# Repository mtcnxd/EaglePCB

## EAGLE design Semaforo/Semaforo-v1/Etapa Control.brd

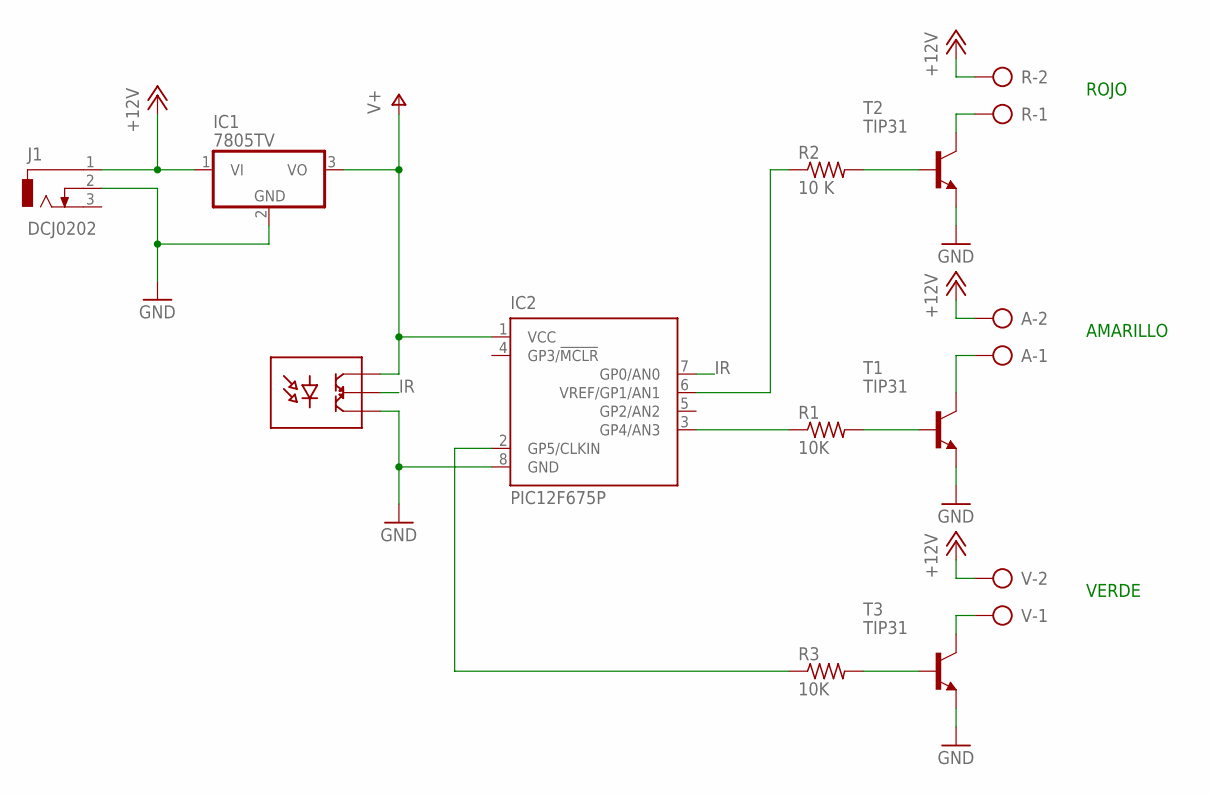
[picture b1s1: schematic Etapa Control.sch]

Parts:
A: AK300/2
IC1: 7805TV; TO220V
IC2: PIC12F675P; DIL8
J1: DCJ0202
LF1838: LF1838
R: AK300/2
R1, R3: 10K; 0204/7
R2: 10 K; 0204/7
T1, T2, T3: TIP31; TO220
V: AK300/2

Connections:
+12V: A.2, IC1.1 (VI), J1.1, R.2, V.2
GND: IC1.2 (GND), IC2.8 (GND), J1.2, LF1838.GND, T1.3 (E), T2.3 (E), T3.3 (E)
IR: IC2.7 (GP0/AN0), LF1838.VOUT
unnamed: R1.2, T1.1 (B)
unnamed: R2.2, T2.1 (B)
unnamed: R3.2, T3.1 (B)
unnamed: T3.2 (C), V.1
unnamed: R.1, T2.2 (C)
unnamed: A.1, T1.2 (C)
unnamed: IC2.6 (VREF/GP1/AN1), R2.1
unnamed: IC2.3 (GP4/AN3), R1.1
unnamed: IC2.2 (GP5/CLKIN), R3.1
V+: IC1.3 (VO), IC2.1 (VCC), LF1838.VCC

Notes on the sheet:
ROJO
AMARILLO
VERDE

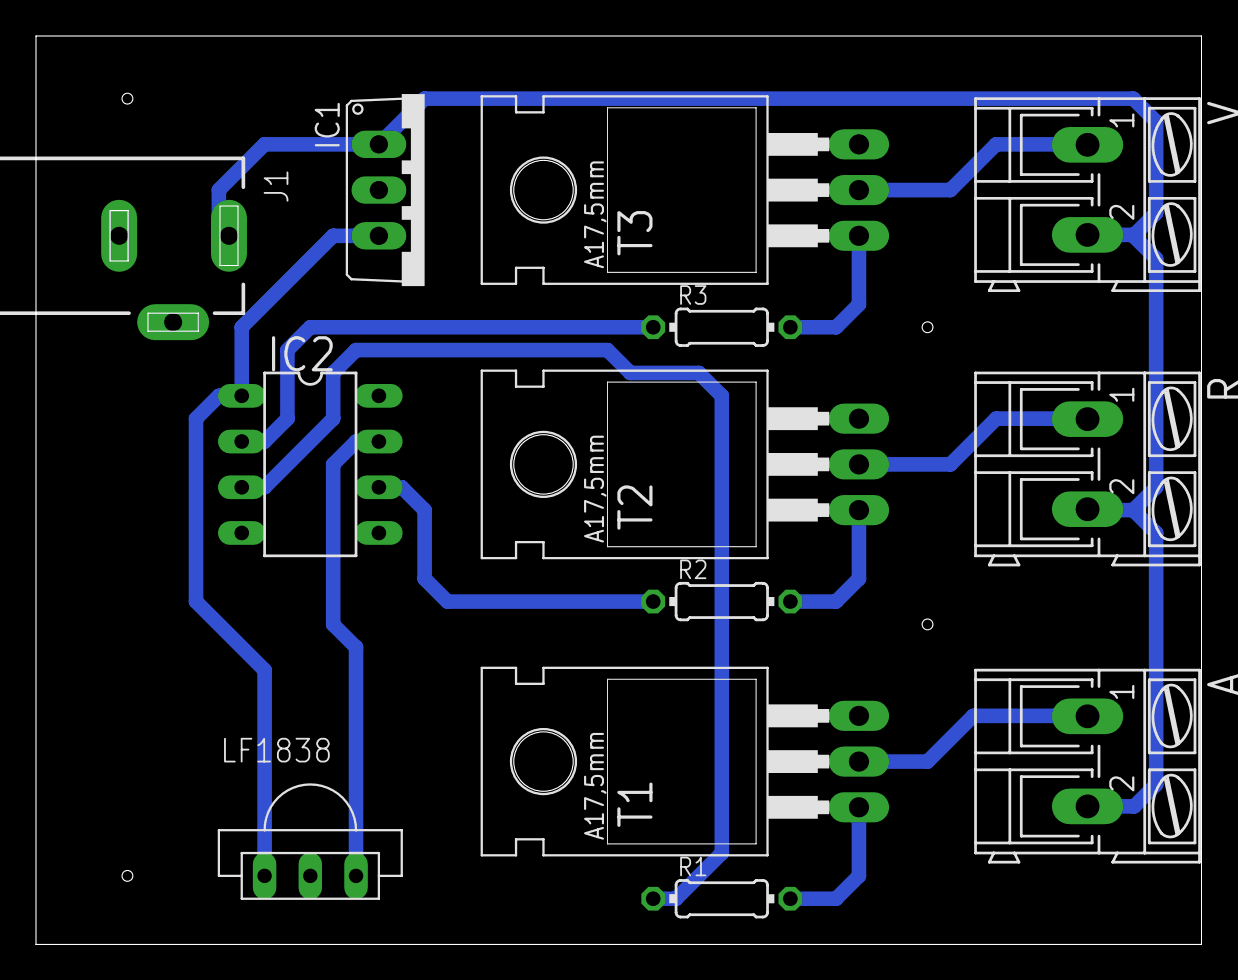
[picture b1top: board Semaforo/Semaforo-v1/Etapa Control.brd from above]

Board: 2 copper layers, 64.8 x 50.5 mm, 13 parts (0 on the bottom side), 13 nets.

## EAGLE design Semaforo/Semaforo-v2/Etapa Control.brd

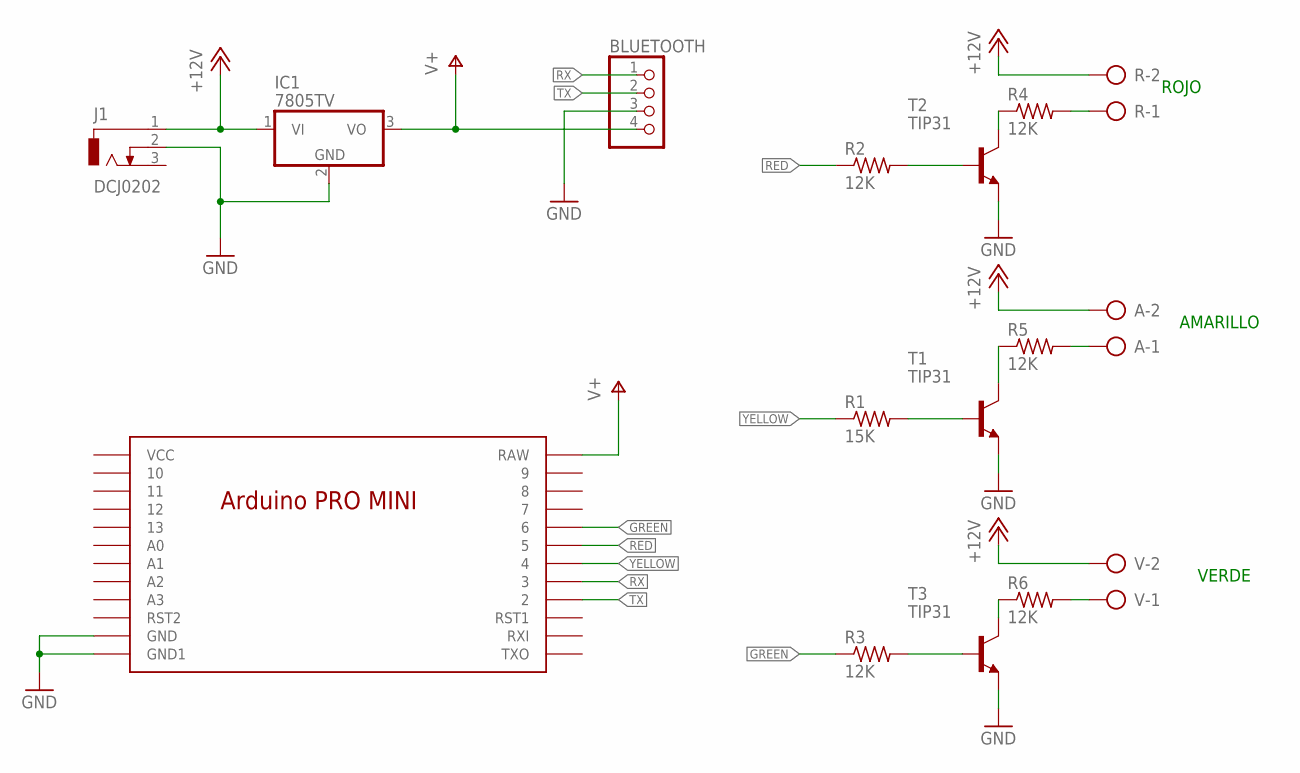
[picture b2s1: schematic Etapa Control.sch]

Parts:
A: AK300/2
BLUETOOTH: PINHD-1X4; 1X04
IC1: 7805TV; TO220V
J1: DCJ0202
R: AK300/2
R1: 15K; 0204/7
R2, R3, R4, R5, R6: 12K; 0204/7
T1, T2, T3: TIP31; TO220
U$1: NANO
V: AK300/2

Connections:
+12V: A.2, IC1.1 (VI), J1.1, R.2, V.2
GND: BLUETOOTH.3, IC1.2 (GND), J1.2, T1.3 (E), T2.3 (E), T3.3 (E), U$1.GND1 (GND), U$1.GND2 (GND1)
GREEN: R3.1, U$1.6
unnamed: R1.2, T1.1 (B)
unnamed: R2.2, T2.1 (B)
unnamed: R3.2, T3.1 (B)
unnamed: R6.1, T3.2 (C)
unnamed: R4.1, T2.2 (C)
unnamed: R5.1, T1.2 (C)
unnamed: R.1, R4.2
unnamed: A.1, R5.2
unnamed: R6.2, V.1
RED: R2.1, U$1.5
RX: BLUETOOTH.1, U$1.3
TX: BLUETOOTH.2, U$1.2
V+: BLUETOOTH.4, IC1.3 (VO), U$1.RAW
YELLOW: R1.1, U$1.4

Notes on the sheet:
ROJO
AMARILLO
VERDE

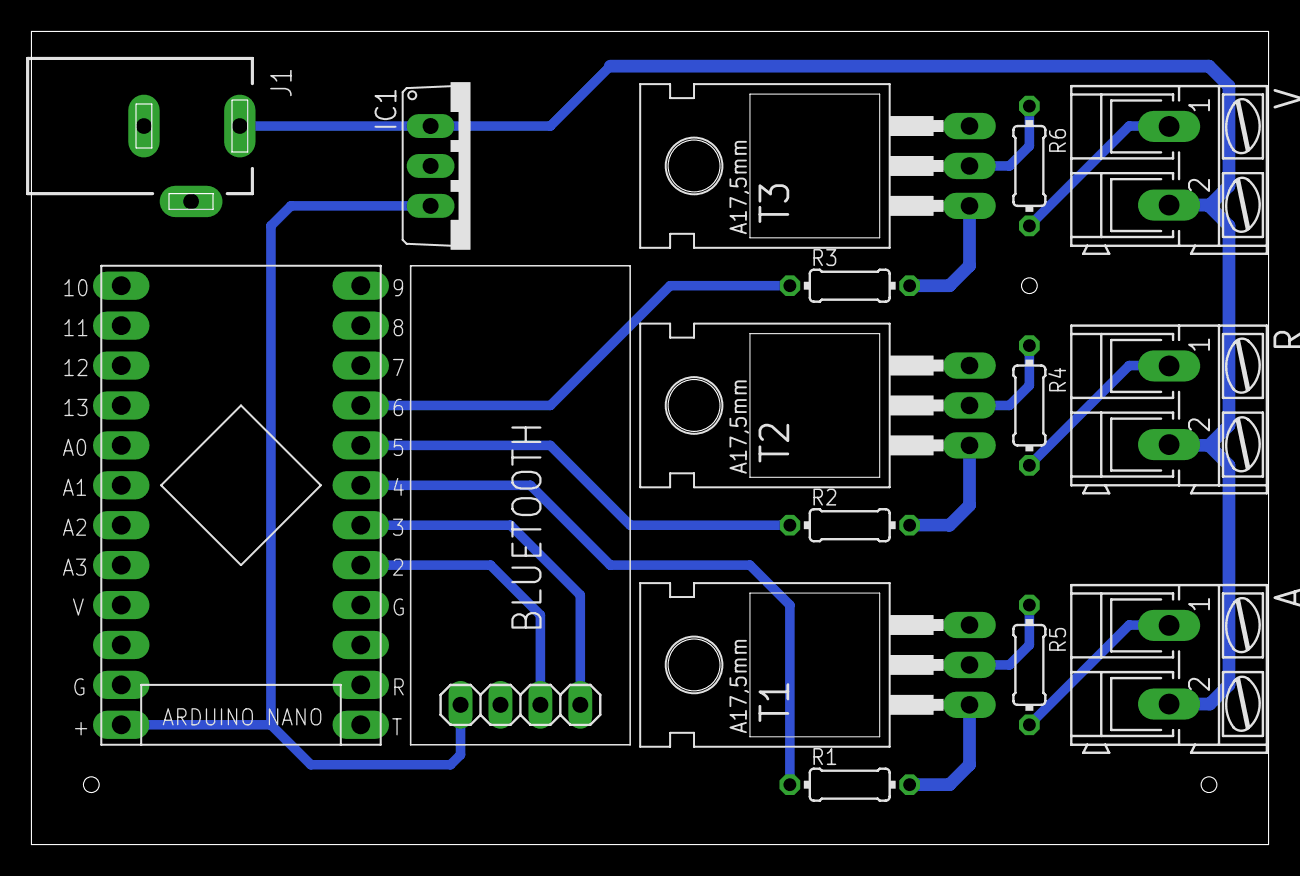
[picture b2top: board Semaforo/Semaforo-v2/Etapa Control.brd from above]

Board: 2 copper layers, 78.7 x 51.7 mm, 16 parts (0 on the bottom side), 17 nets.

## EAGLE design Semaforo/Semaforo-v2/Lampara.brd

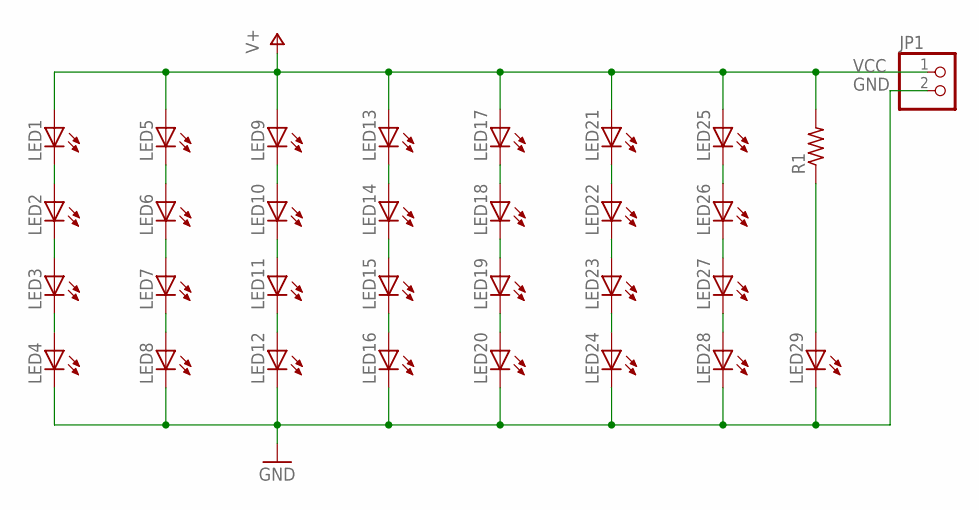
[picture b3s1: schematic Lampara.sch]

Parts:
JP1: PINHD-1X2/90; 1X02/90
LED1, LED2, LED3, LED4, LED5, LED6, LED7, LED8, LED9, LED10, LED11, LED12, LED13, LED14, LED15, LED16, LED17, LED18, LED19, LED20, LED21, LED22, LED23, LED24, LED25, LED26, LED27, LED28, LED29: LED5MM
R1: R-US_0204/7; 0204/7

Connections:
GND: JP1.2, LED4.K (C), LED8.K (C), LED12.K (C), LED16.K (C), LED20.K (C), LED24.K (C), LED28.K (C), LED29.K (C)
unnamed: LED15.K (C), LED16.A
unnamed: LED1.K (C), LED2.A
unnamed: LED2.K (C), LED3.A
unnamed: LED3.K (C), LED4.A
unnamed: LED5.K (C), LED6.A
unnamed: LED6.K (C), LED7.A
unnamed: LED7.K (C), LED8.A
unnamed: LED10.K (C), LED11.A
unnamed: LED9.K (C), LED10.A
unnamed: LED11.K (C), LED12.A
unnamed: LED14.K (C), LED15.A
unnamed: LED13.K (C), LED14.A
unnamed: LED25.K (C), LED26.A
unnamed: LED17.K (C), LED18.A
unnamed: LED18.K (C), LED19.A
unnamed: LED29.A, R1.1
unnamed: LED19.K (C), LED20.A
unnamed: LED22.K (C), LED23.A
unnamed: LED23.K (C), LED24.A
unnamed: LED27.K (C), LED28.A
unnamed: LED26.K (C), LED27.A
unnamed: LED21.K (C), LED22.A
VCC: JP1.1, LED1.A, LED5.A, LED9.A, LED13.A, LED17.A, LED21.A, LED25.A, R1.2

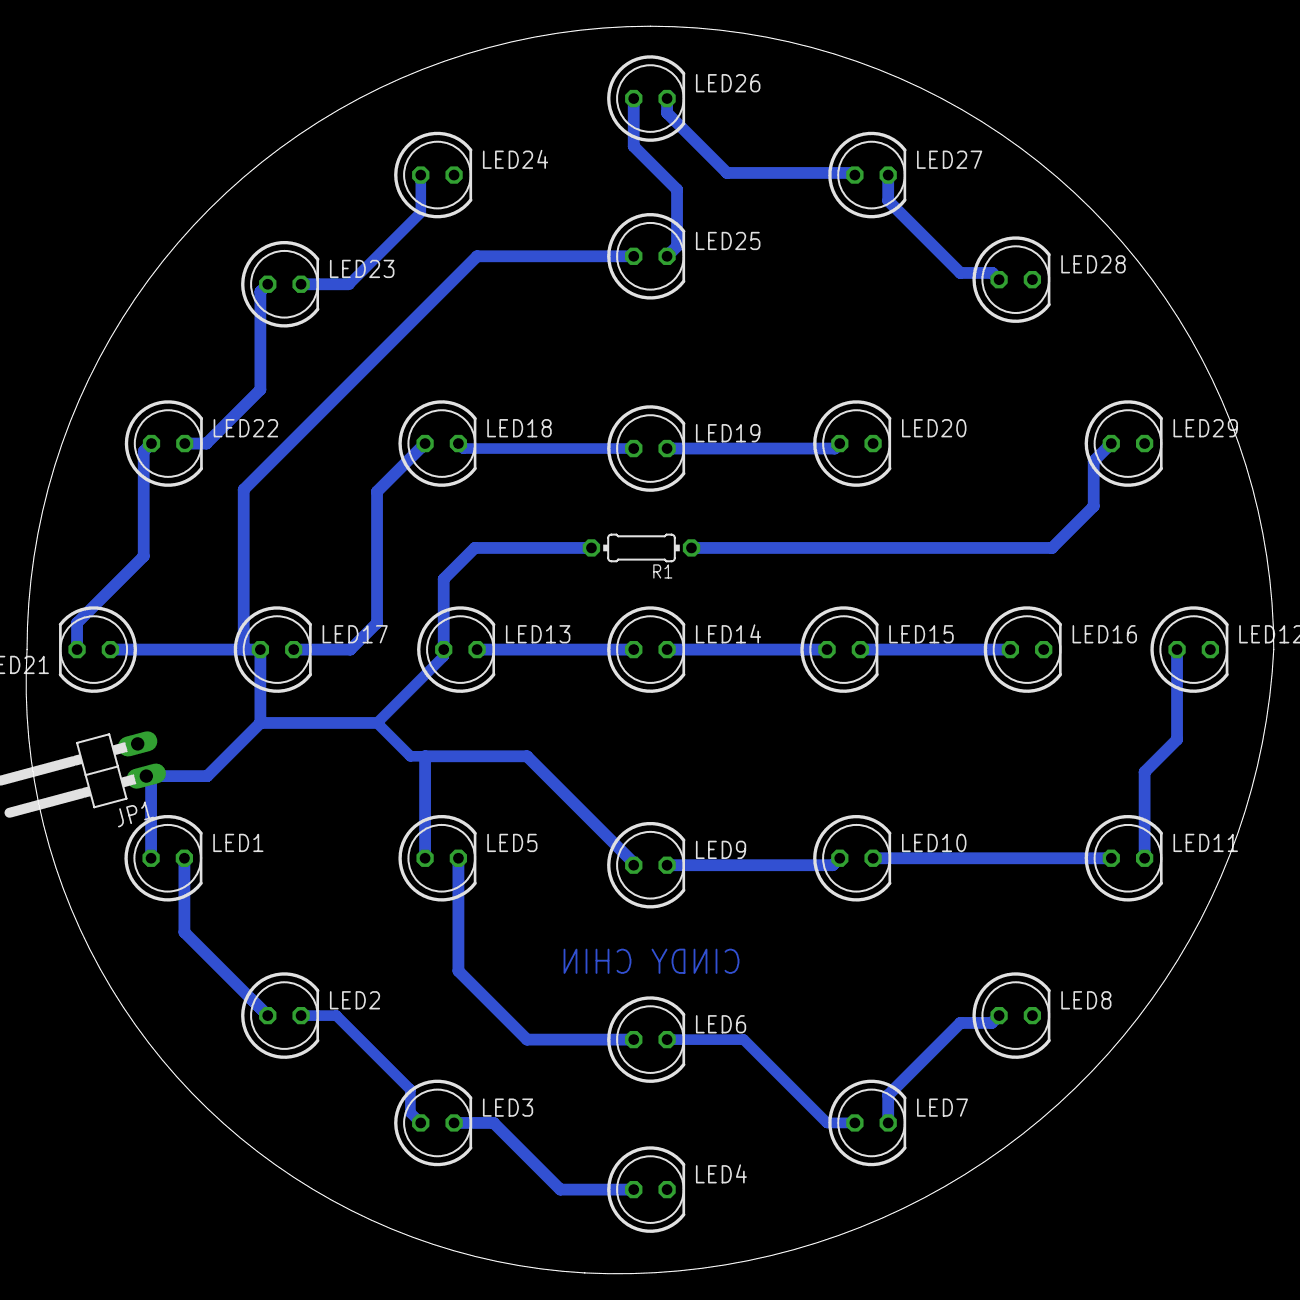
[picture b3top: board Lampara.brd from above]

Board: 2 copper layers, 95.1 x 95.1 mm, 31 parts (0 on the bottom side), 24 nets.

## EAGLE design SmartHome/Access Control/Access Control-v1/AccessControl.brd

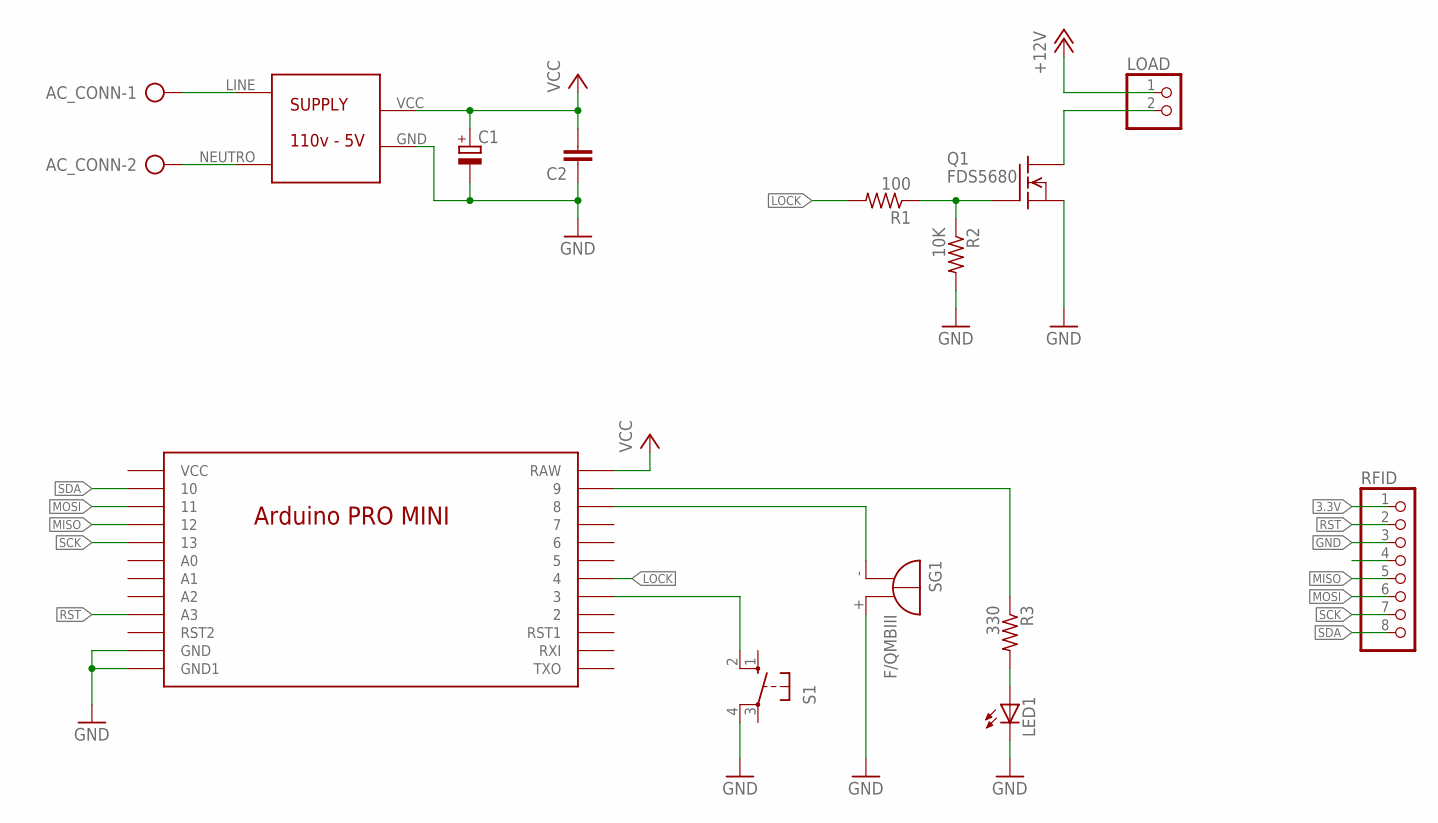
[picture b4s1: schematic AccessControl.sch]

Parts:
AC_CONN: AK300/2
C1: CPOL-EUE2.5-6; E2,5-6
C2: C2.5/2; C2.5-2
LED1: LED3MM
LOAD: PINHD-1X2; 1X02
Q1: FDS5680; SO-8
R1: 100; 0204/7
R2: 10K; 0204/7
R3: 330; 0204/7
RFID: PINHD-1X8; 1X08
S1: 10-XX; B3F-10XX
SG1: F/QMBIII
U$1: NANO
U$2: SUPPLY5V

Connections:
3.3V: RFID.1
+12V: LOAD.1
GND: C1.-, C2.1, LED1.K (C), Q1.1 (S), Q1.2 (S), Q1.3 (S), R2.2, RFID.3, S1.4 (P1), SG1.+ (-), U$1.GND1 (GND), U$1.GND2 (GND1), U$2.GND
LOCK: R1.2, U$1.4
MISO: RFID.5, U$1.12
MOSI: RFID.6, U$1.11
unnamed: Q1.4 (G), R1.1, R2.1
unnamed: AC_CONN.2, U$2.NEUTRO
unnamed: LOAD.2, Q1.5 (D), Q1.6 (D), Q1.7 (D), Q1.8 (D)
unnamed: LED1.A, R3.2
unnamed: AC_CONN.1, U$2.LINE
unnamed: SG1.- (+), U$1.8
unnamed: S1.2 (S1), U$1.3
unnamed: R3.1, U$1.9
NC: RFID.4
RST: RFID.2, U$1.A3
SCK: RFID.7, U$1.13
SDA: RFID.8, U$1.10
VCC: C1.+, C2.2, U$1.RAW, U$2.VCC

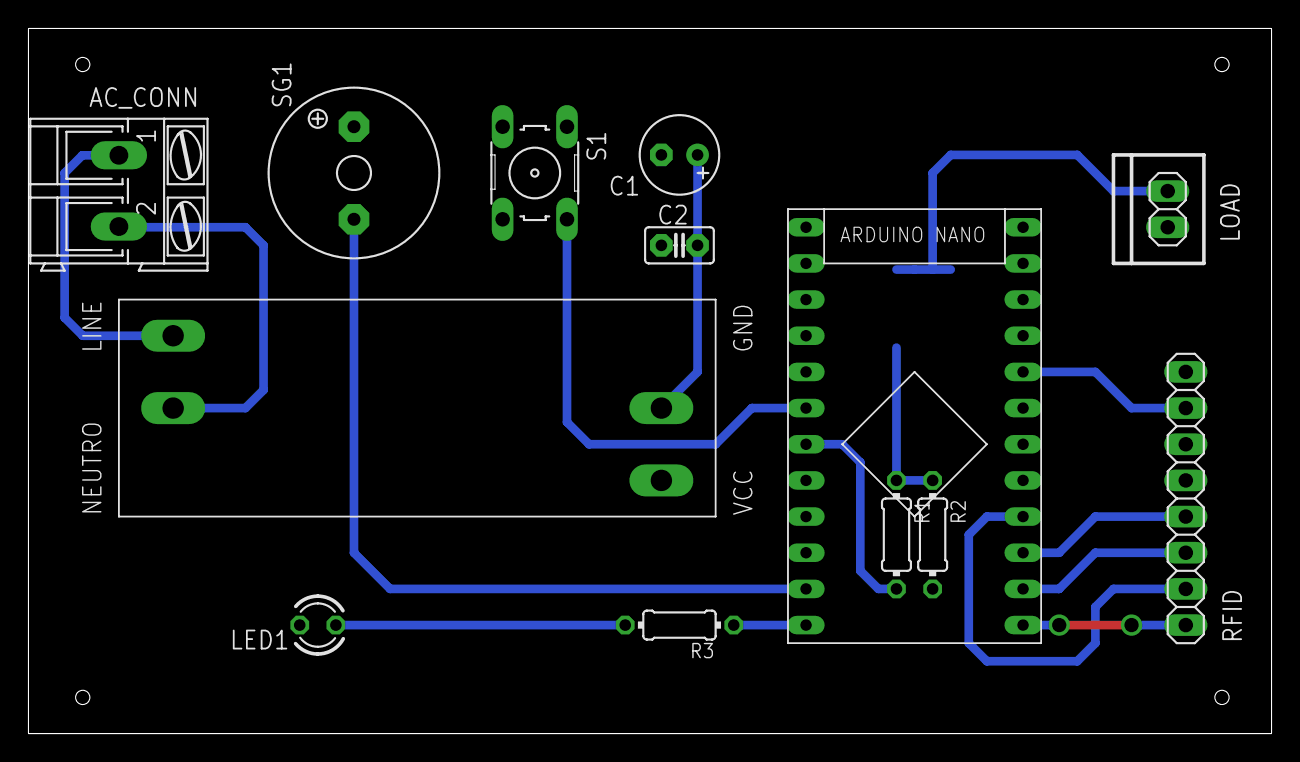
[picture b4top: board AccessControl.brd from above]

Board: 2 copper layers, 87.3 x 49.5 mm, 14 parts (1 on the bottom side), 16 nets.

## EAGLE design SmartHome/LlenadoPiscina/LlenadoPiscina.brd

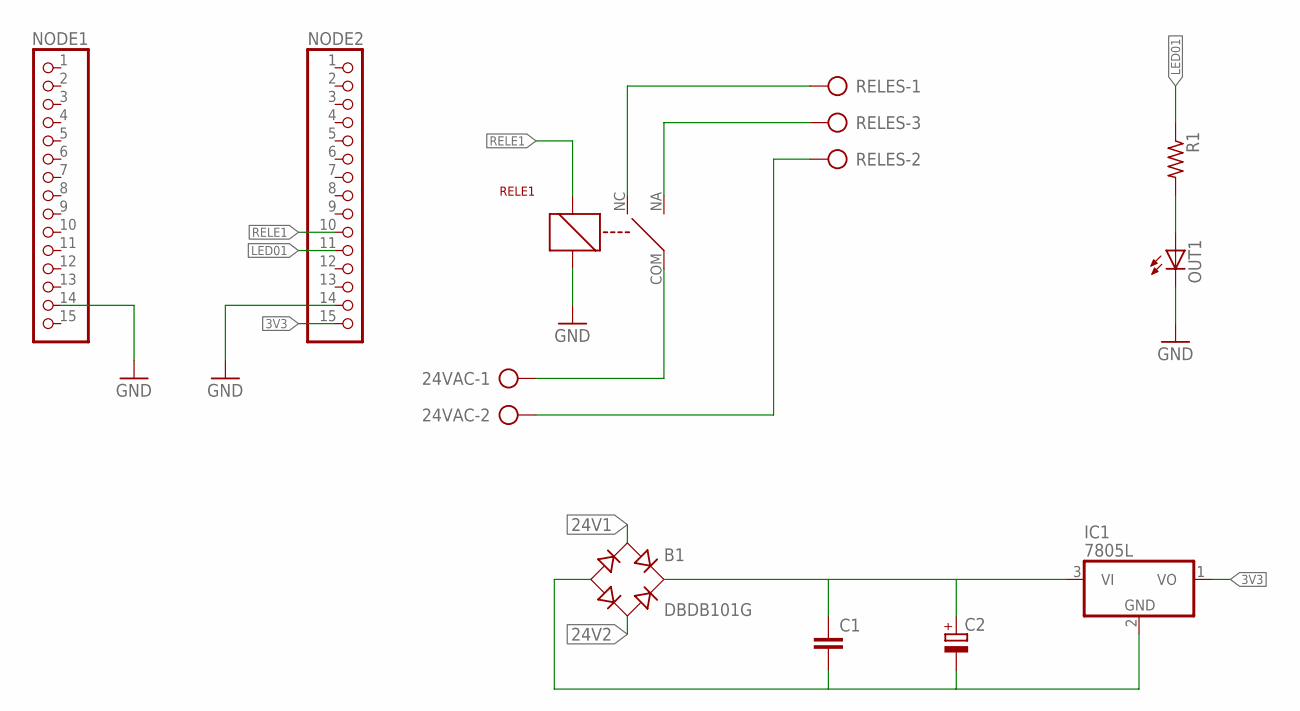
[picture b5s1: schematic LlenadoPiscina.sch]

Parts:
24VAC: AK500/2-H
B1: DBDB101G; DB
C1: C2.5/2; C2.5-2
C2: CPOL-EUE2,5-6E; E2,5-6E
IC1: 7805L; TO92
NODE1, NODE2: PINHD-1X15; 1X15
OUT1: LED3MM
R1: R-US_0204/7; 0204/7
RELE1: RAS0510
RELES: AK500/3-H

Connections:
3V3: IC1.1 (VO), NODE2.15
24V1: 24VAC.1, B1.AC1, RELE1.COM
24V2: 24VAC.2, B1.AC2, RELES.2
GND: NODE1.14, NODE2.14, OUT1.K (C), RELE1.B2
LED01: NODE2.11, R1.1
unnamed: RELE1.NC, RELES.1
unnamed: RELE1.NA, RELES.3
unnamed: OUT1.A, R1.2
unnamed: B1.+, C1.1, C2.+, IC1.3 (VI)
unnamed: B1.-, C1.2, C2.-, IC1.2 (GND)
RELE1: NODE2.10, RELE1.B1

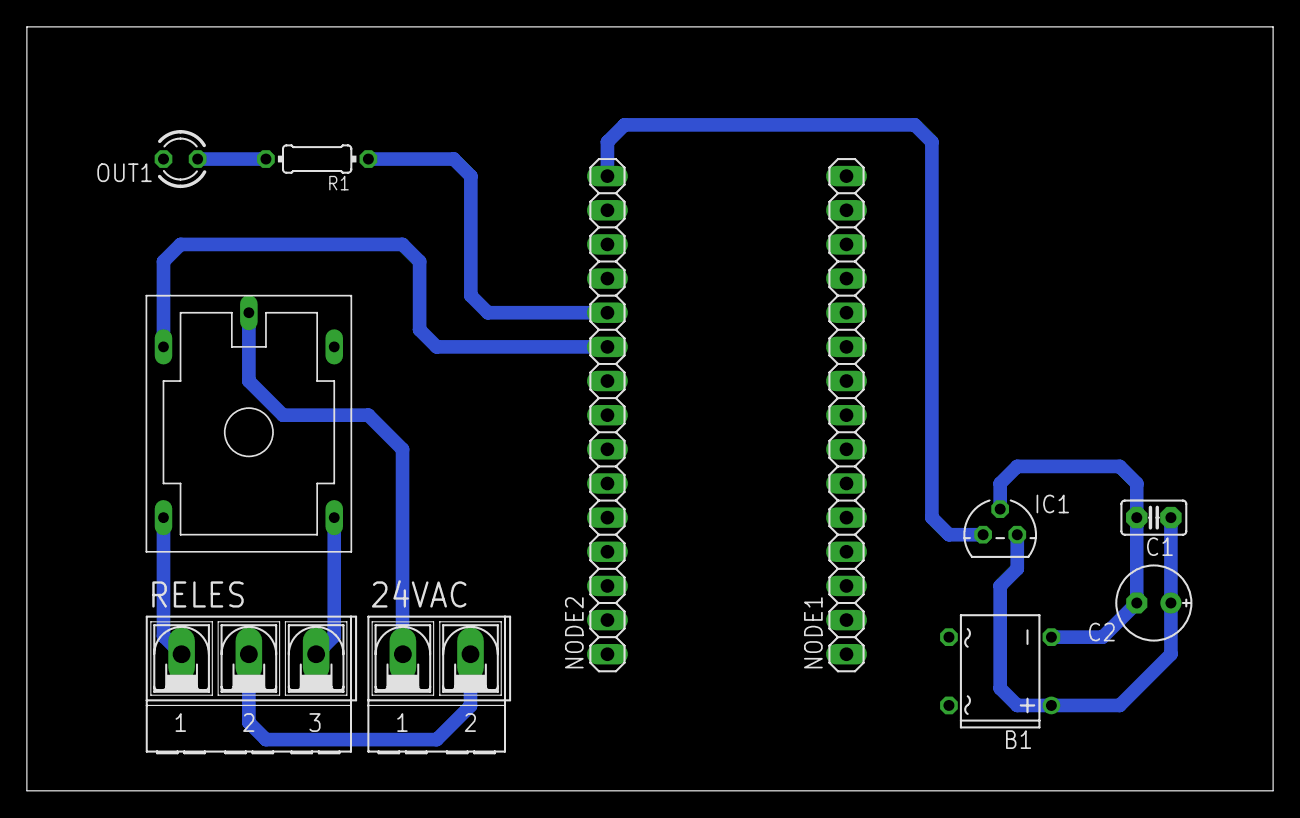
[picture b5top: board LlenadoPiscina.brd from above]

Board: 2 copper layers, 92.7 x 56.8 mm, 11 parts (0 on the bottom side), 11 nets.

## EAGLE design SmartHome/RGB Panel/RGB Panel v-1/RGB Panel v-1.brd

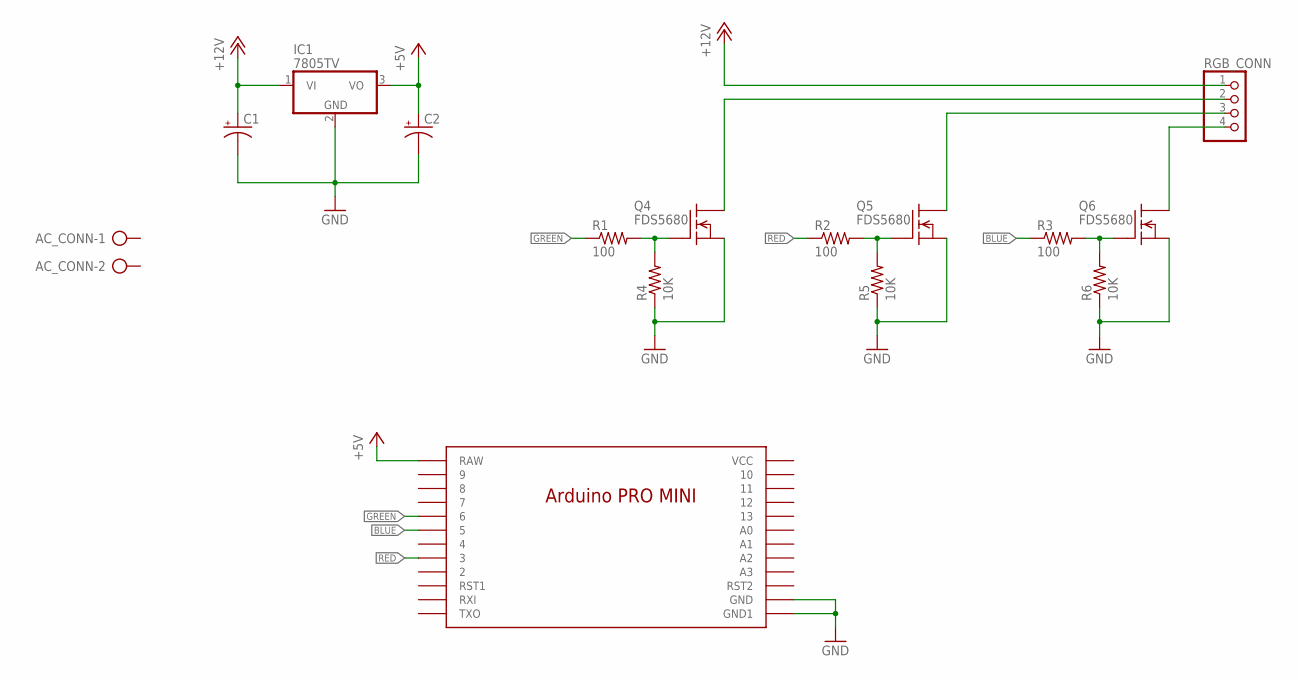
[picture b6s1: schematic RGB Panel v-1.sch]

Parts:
AC_CONN: AK300/2
C1, C2: CPOL-USE2,5-6E; E2,5-6E
IC1: 7805TV; TO220V
Q4, Q5, Q6: FDS5680; SO-8
R1, R2, R3: 100; 0204/7
R4, R5, R6: 10K; 0204/7
RGB_CONN: PINHD-1X4; 1X04
U$1: NANO

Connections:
+5V: C2.+, IC1.3 (VO), U$1.RAW
+12V: C1.+, IC1.1 (VI), RGB_CONN.1
BLUE: R3.1, U$1.5
GND: C1.-, C2.-, IC1.2 (GND), Q4.1 (S), Q4.2 (S), Q4.3 (S), Q5.1 (S), Q5.2 (S), Q5.3 (S), Q6.1 (S), Q6.2 (S), Q6.3 (S), R4.1, R5.1, R6.1, U$1.GND1 (GND), U$1.GND2 (GND1)
GREEN: R1.1, U$1.6
unnamed: Q4.4 (G), R1.2, R4.2
unnamed: Q5.4 (G), R2.2, R5.2
unnamed: Q6.4 (G), R3.2, R6.2
unnamed: Q4.5 (D), Q4.6 (D), Q4.7 (D), Q4.8 (D), RGB_CONN.2
unnamed: Q5.5 (D), Q5.6 (D), Q5.7 (D), Q5.8 (D), RGB_CONN.3
unnamed: Q6.5 (D), Q6.6 (D), Q6.7 (D), Q6.8 (D), RGB_CONN.4
RED: R2.1, U$1.3

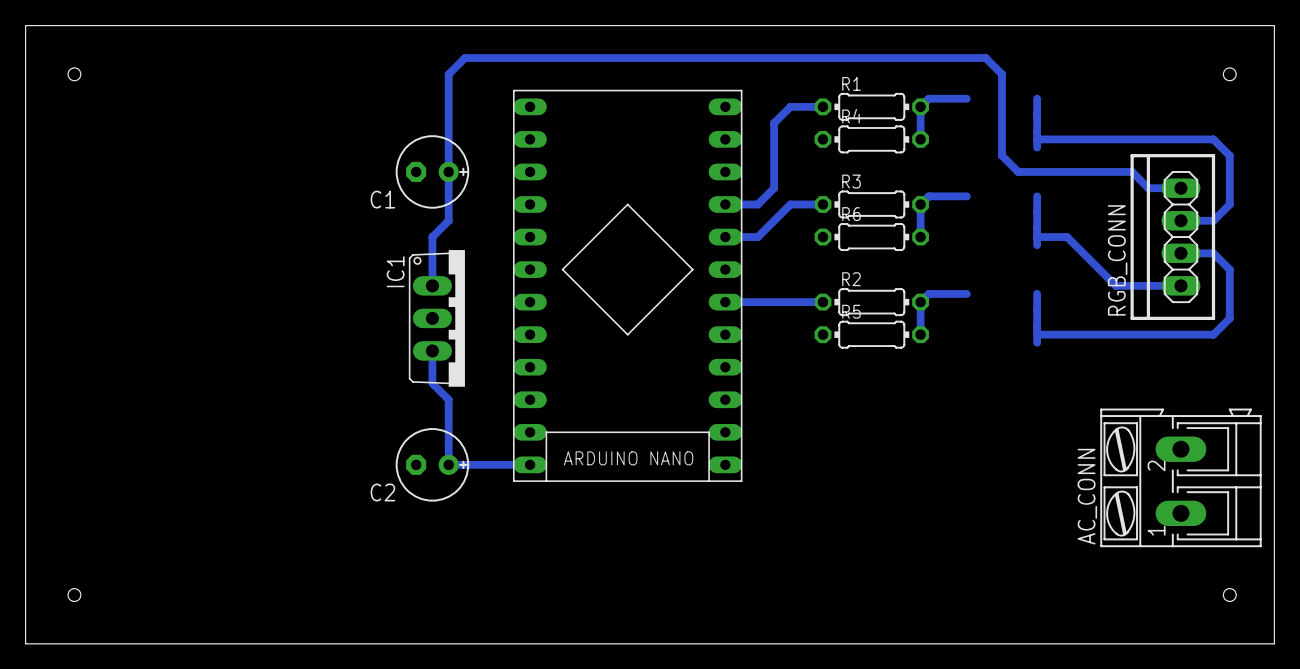
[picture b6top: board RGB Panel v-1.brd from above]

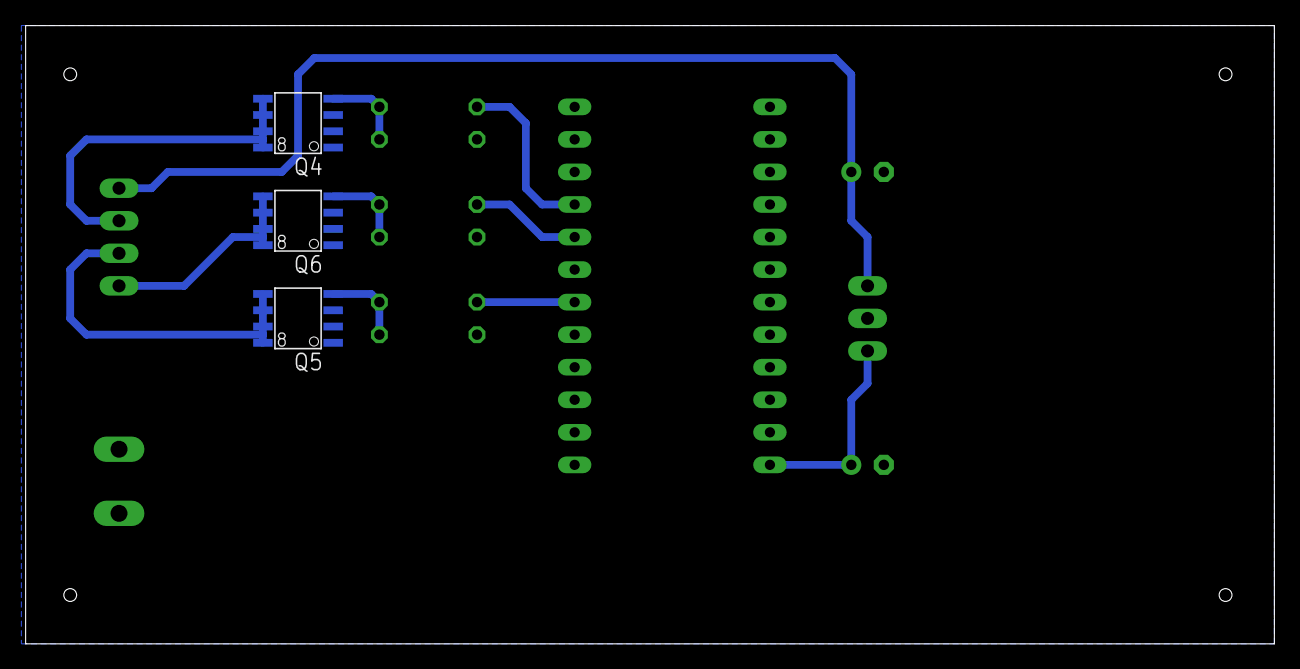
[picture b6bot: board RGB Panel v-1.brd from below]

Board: 2 copper layers, 97.5 x 48.2 mm, 15 parts (3 on the bottom side), 12 nets.
